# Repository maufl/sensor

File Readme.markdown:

# Simple ESP based sensor board
This is just my toy project to learn about designing PBC, electrical engineering and embedded software development.
Right now it's a ESP8266 based board with a temperature and humidity sensor.
In the long run I want to have a generic base design with an ESP32 that runs well on battery for a long time and where I can add any sensor or actor I want.

**Archived because I started a new repository**

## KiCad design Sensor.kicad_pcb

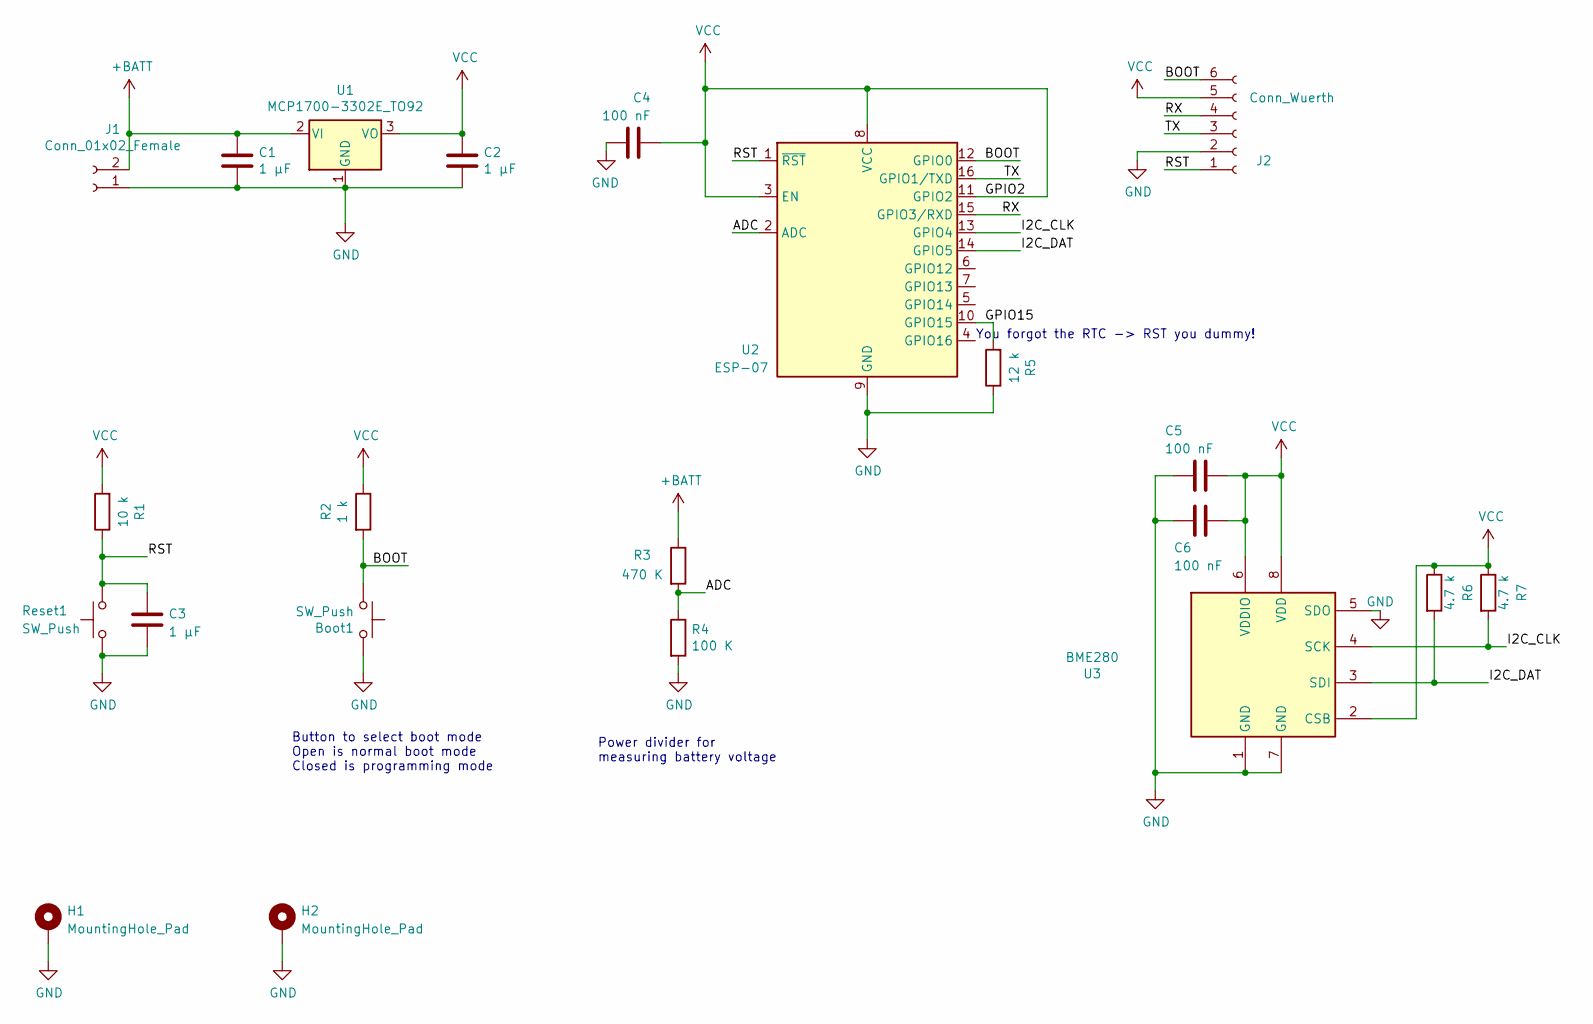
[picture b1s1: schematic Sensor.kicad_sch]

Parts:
Boot1: SW_Push; SW_SPST_B3U-1000P
C1, C2, C3: 1 µF; C_0603_1608Metric
C4, C5, C6: 100 nF; C_0603_1608Metric
H1, H2: MountingHole_Pad; MountingHole_2.2mm_M2_DIN965_Pad
J1: Conn_01x02_Female; JST_PH_S2B-PH-K_1x02_P2.00mm_Horizontal
J2: Conn_Wuerth; Würth_Debug_Connector_6pin
R1: 10 k; R_0603_1608Metric
R2: 1 k; R_0603_1608Metric
R3: 470 K; R_0603_1608Metric
R4: 100 K; R_0603_1608Metric
R5: 12 k; R_0603_1608Metric
R6, R7: 4.7 k; R_0603_1608Metric
Reset1: SW_Push; SW_SPST_B3U-1000P
U1: MCP1700-3302E_TO92; SOT-23
U2: ESP-07
U3: BME280; Bosch_LGA-8_2.5x2.5mm_P0.65mm_ClockwisePinNumbering

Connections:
+BATT: C1.1, J1.2, R3.1, U1.2 (VI)
/ADC: R3.2, R4.1, U2.2 (ADC)
/BOOT: Boot1.1, J2.6, R2.2, U2.12 (GPIO0); also elsewhere on the board
/GPIO15: R5.2, U2.10 (GPIO15)
/I2C_CLK: R7.2, U2.13 (GPIO4), U3.4 (SCK)
/I2C_DAT: R6.2, U2.14 (GPIO5), U3.3 (SDI)
/RST: C3.1, J2.1, R1.1, Reset1.2, U2.1 (~RST); also elsewhere on the board
/RX: J2.4, U2.15 (GPIO3/RXD)
/TX: J2.3, U2.16 (GPIO1/TXD)
GND: Boot1.2, C1.2, C2.2, C3.2, C4.1, C5.2, C6.2, H1.1, H2.1, J1.1, J2.2, R4.2, R5.1, Reset1.1, U1.1 (GND), U2.9 (GND), U3.1 (GND), U3.5 (SDO), U3.7 (GND); also elsewhere on the board
VCC: C2.1, C4.2, C5.1, C6.1, J2.5, R1.2, R2.1, R6.1, R7.1, U1.3 (VO), U2.3 (EN), U2.8 (VCC), U2.11 (GPIO2), U3.2 (CSB), U3.6 (VDDIO), U3.8 (VDD)

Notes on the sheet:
Button to select boot mode Open is normal boot mode Closed is programming mode
Power divider for measuring battery voltage
You forgot the RTC -> RST you dummy!

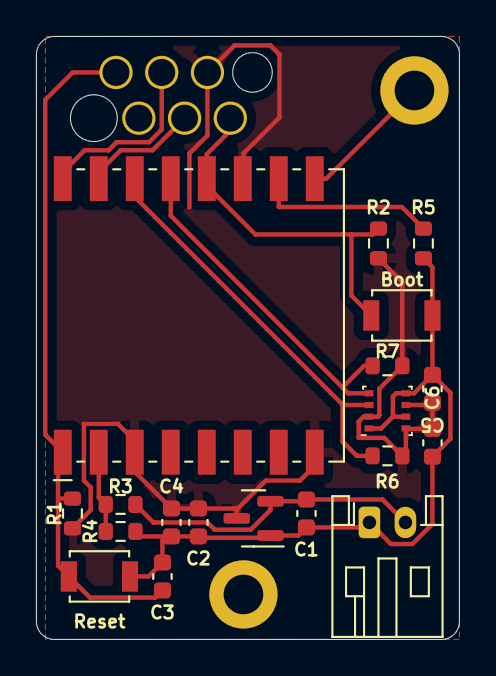
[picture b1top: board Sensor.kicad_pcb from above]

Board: 2 copper layers, 23.5 x 33.5 mm, 22 parts (1 on the bottom side), 11 nets.

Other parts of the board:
Boot: SW_Push; SW_SPST_B3U-1000P
Reset: SW_Push; SW_SPST_B3U-1000P

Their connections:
/BOOT: Boot.1; also elsewhere on the board
/RST: Reset.2; also elsewhere on the board
GND: Boot.2, Reset.1; also elsewhere on the board

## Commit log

2023-09-12 Add readme
